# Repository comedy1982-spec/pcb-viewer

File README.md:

# AllinOneDesign

**요구사항 한 줄에서 시스템 다이어그램 → 회로 → PCB → 기구(하우징)까지, 브라우저 하나에서 AI와 함께 설계하는 단일 HTML 도구**입니다. 파일은 브라우저 안에서만 처리되며 서버로 전송되지 않습니다.

- 실행: `dist/index.html`을 브라우저로 엽니다 (3D·zip·엑셀 라이브러리만 CDN에서 불러오므로 인터넷 연결 필요).
- 사용 설명서: [docs/manual.html](docs/manual.html) · 기능 상세 노트(버전별): [docs/DETAILS.md](docs/DETAILS.md)
- 예제: SENSE-32, MCU DC 모터(MOTION-32 DEV), MCU BLDC 3상(MOTION-32 BLDC), AURIX TC364 인버터 — 첫 화면의 예제 칩으로 엽니다.

## 주요 기능

### 1. 단계별 설계 (신규 설계)
| 단계 | 하는 일 | 결과물 |
|---|---|---|
| **1 시스템 다이어그램** | 프로젝트 이름·요구사항을 적으면 AI가 분석하고, 빠진 필수 정보(전원·MCU·통신·기능·환경)는 **응답형 질문 카드**로 물어본 뒤 HW 블록 다이어그램을 그립니다. 블록·기능·인터페이스를 명령 또는 패널에서 편집합니다. | HW 블록 다이어그램 (SVG) |
| **2 회로** | 다이어그램을 **저가형 · 표준 · 확장형** 세 회로 안으로 풀어 BOM 참고가·부품 수·여유 MCU 핀·레귤레이터 손실·점수를 비교하고 하나를 고릅니다. 실제 부품 선정 · 넷리스트 · MCU 핀 배정 · 회로도가 만들어지며, **데이터시트 탭**에서 부품별 정리 페이지(HTML DB)를 봅니다. | 회로도(여러 시트) · 넷리스트 · BOM |
| **3 PCB** | 층 수(2–10) · 보드 크기(최소화/자동/직접) · 배치 전략을 고르면 자동 배치·배선합니다. 부품 끌어 옮기기·배선·비아·DRC·래츠네스트 편집, 내층을 포함한 **층별 보기**, 핀 스왑으로 회로와 함께 수정. | 배치·배선된 보드 (KiCad 저장) |
| **모터 파워 스테이지** | DC 모터 H-브리지(게이트 드라이버 ×2 + 외부 N-MOSFET ×4)·3상 인버터(×3 + ×6)를 전류 등급에 맞춰 FET 병렬·션트·전류 앰프·벌크·역전압 P-FET까지 회로로 생성, 트레이스 폭에 모터 전류 반영. | 회로도 · BOM |
| **부품 핀** | 라이브러리에 핀이 없으면 데이터시트 PDF를 올려 핀 표를 읽어 저장(pdf.js, 패키지별 표 선택, AI 모드 Claude 판독) — `datasheet <MPN>`, add part / replace, 라이브러리 버튼. | 핀 배열 → 회로 |
| **1 안전 목표** | ASIL ≠ QM이면 안전 목표(SG)를 고르고 위반 경로 블록에 태그, 구조 변형 3안(단일 MCU+외부 감시 · 메인+세이프티 MCU · ASIL 분해 2채널)을 DC·FTTI·원가로 비교해 적용, 규칙으로 검증(감지·독립 차단·FTTI·독립성·공통 원인). | SG 태그 · 검증 ✓/✗ |
| **4 기구 CAD** | 보드를 감싸는 보호 하우징을 Text-to-CAD로 설계합니다(시안 A 다이캐스팅·B 사출 스냅핏·C 압출 프로파일·D 하이브리드, 재질 6종·IP·진동·발열 조건, 구멍·글랜드·벤트·탭·리브·핀·각인, 둥근모따기/각모따기). 3D에서 요소를 **선택해 AI에게 지시**하고, 조립도·부품도(베이스/커버)·기구 BOM·SCAD/STL을 냅니다. | 하우징 3D · 도면 · BOM · SCAD |

기존 프로젝트(KiCad `.kicad_pcb`·회로도, PADS Logic 회로도, Gerber, 뷰어 JSON)도 같은 단계 표시줄로 오갑니다. 1단계는 보드에서 추출한 HW 블록 다이어그램입니다.

### 2. AI 설계 도우미
- 오른쪽 도킹 패널의 **설계 도우미**가 네 단계의 콘솔(시스템·회로도·배치/배선·Text-to-CAD)을 하나의 대화로 합칩니다. 결정론 모드는 문장을 규칙으로 명령으로 바꾸고, AI 모드는 Claude가 같은 명령을 골라 실행합니다.
- 설계를 바꾼 실행마다 **변경 요청 카드**가 붙습니다: 시스템·회로·PCB·HSIS·기구·BOM 영향, 변경 요약, 실행한 명령. **승인**하면 `CR-n` 리비전으로 기록되고, **되돌리기**는 그 실행만 정확히 되돌립니다.
- 기구 CAD에서는 3D나 형상 트리에서 요소를 고른 뒤(Shift/Ctrl 다중) "이거 M20으로 키우고 윗면은 R2"처럼 지시합니다.
- **등급 부품 자동 적용**: ASIL 프로젝트는 회로 생성 때 상용 부품을 핀 호환 차량용(AEC-Q100/Q101/Q200) 부품으로 바꾸고, `safety parts [--apply]`가 등급 미달·미상 부품과 대체품을 점검·일괄 교체합니다. 부품 레코드에 등급·온도·ASIL·FIT 필드(CSV·Claude 추정·API).
- **기능 안전(ASIL)**: 요구사항의 ASIL A~D를 읽어 시스템·블록 등급(배지·세이프 스테이트 경로·FFI 경계)을 다이어그램에 얹고, 등급별 권장 안전 메커니즘(전원 감시·외부 워치독·fault 리드백·SBC·이중 차단·리던던트 센서·2채널)을 블록으로 추가해 회로 부품(TPS3823 감시/워치독, 하이사이드 차단 스위치)까지 생성합니다. 회로·PCB 콘솔 `safety check`/`safety fmeda`가 등급별 회로 점검과 FIT·DC·SPFM·PMHF 추정을 내고 보고서·Excel·HSIS에 실립니다.
- **회로 해석(analyze)**: 전원 트리 · 디커플링 감사 · RC/LC·분압·LED 패턴 · 수동 소자 AC 주파수 응답 · DC 동작점(MNA) · IR drop · 신호 무결성 · 열 · EMC를 조회 명령으로 열어, 질문 모드의 Claude가 "필터 컷오프 얼마야?", "레일 전압 강하는?"에 계산값으로 답합니다.
- **아무 부품이나 추가**: "CC2420 추가해줘" → 라이브러리/Claude 추정의 핀 배열로 심볼을 만들고 전원·접지 자동 연결, 나머지 핀은 `connect`로, `apply`로 보드에(패키지 이름으로 풋프린트 생성).
- **보드 모양**: 사각형 외에 라운드·원형·타원·L자·T자·육각·팔각·다각형과 컷아웃(구멍) — 시작 카드에서 고르거나 `board shape …`/"원형 60mm로".
- **제품 프로필**: "EPS ECU 설계"처럼 제품만 적어도 표준 블록 구성(전원·SBC·락스텝 MCU·CAN-FD·인버터·페이즈 컷·센서 IF…)을 먼저 깔고, 블록별로 갈리는 것(타입·센서 IF·리던던시…)만 묻습니다. AI 모드는 어떤 제품이든, 규칙 모드는 EPS·BMS·BCM·인버터 템플릿.
- **로컬 AI**: claude.ai 밖(내려받은 파일·`npm run serve`)에서는 [Claude 허용] → 로컬 AI 설정에 API 키(또는 프록시)를 넣으면 같은 AI 모드가 Messages API로 동작합니다. `npm run serve:copilot`이면 API 키 없이 **GitHub Copilot** 구독(Copilot CLI 로그인)으로 동작합니다.
- **회로 보강 명령**: "HSIS 기준으로 테스트 포인트 전부 달아줘"(`tp`), "안 쓰는 핀 10k로 GND에"(`tie`), "전원 입력에 페라이트 비드"(`insert`), `add C --pins U1.12,GND`처럼 핀을 직접 지정 — AI 모드가 이 명령들로 풀어 실행하고 보드에 반영(`apply`)까지 합니다. TP는 HSIS 표의 TP 열·검사에 연결됩니다.
- **부품 교체(대화형)**: "U2를 AP2112K-3.3으로 바꿔줘"라고 하면 승인 부품 목록 → 내장 DB → Claude 추정 → 부품 API(Mouser·Nexar·사내 서버) 순으로 부품을 찾고, 핀 대응(이름·역할·번호)을 표로 확인받은 뒤 회로도·보드(풋프린트 자동 생성)·BOM·데이터시트·HSIS를 한 번에 바꿉니다. 머리글 **부품** 창에서 회사 승인 부품 목록(CSV/Excel)을 가져오고 추정 결과를 승인·내보냅니다.

### 3. 보기 · 분석
- **3D / TOP / BOTTOM / 층별(내층 포함) / 회로도**, 나란히 보기, 여러 보기를 격자로 띄우는 **새 창**(시스템 다이어그램·기구 3D·기구 도면·HSIS·시뮬레이션 포함, 메인 창과 연동).
- **지표 띠**: BOM 참고가, 가이드라인 점수, DRC·미배선, HSIS 정상/전체, 최고 Tj, 하우징 무게·IP — 누르면 해당 화면으로.
- **전체 보기**: 네 단계의 그림과 수치가 화살표로 이어진 한 화면, AI 바 포함.
- **시뮬레이션**: 전압 강하(IR drop), 신호 무결성, 열 분포, EMC/EMI, 회로 동작(MNA + 펌웨어 코시뮬레이션: LED·모터가 3D에서 움직임).
- **설계 가이드라인** 점검(회로·PCB 프리셋), DRC.

### 4. HSIS (HW/SW 인터페이스 사양)
- 엑셀 HSIS와 AUTOSAR ARXML을 읽어 **신호 표 · MCU 핀 맵 · 추적성(요구사항↔테스트) · 검사 결과 · 핀 추천(헝가리안 매칭) · MCAL 설정 · 테스트 케이스(SWE.6/SYS.4)**를 만들고 회로도·보드·펌웨어와 대조합니다.
- 보드에 HSIS가 없으면 MCU 핀과 넷으로 초안을 만듭니다.

### 5. 멀티보드 시스템
- 메인 + 센서 보드처럼 **보드 둘 이상을 커넥터로 잇는 제품**을 한 시스템으로 묶습니다. 머리글의 보드 선택 상자로 보드를 추가(파일·신규 설계·예제)하고 오갑니다.
- **시스템 연결** 탭: 보드·커넥터 짝으로 연결(케이블/B2B)을 만들고 핀을 번호·넷 이름·직접으로 매핑, 핀 수·짝 없는 핀·접지/전원/신호 충돌·레일 전압·차동 쌍 점검, 보드 연결도(SVG/PNG), 시스템 넷, 시스템 BOM(보드별 수량) → Excel·보고서.

### 6. 리비전 기록 · 비교
- 설계가 바뀌면 자동으로 리비전이 쌓이고(원인·단계·변경 요약 포함), 이름·단계(Proto~MP)·메모를 붙여 저장할 수 있습니다.
- **비교**: 요약 · 부품 · 배치 · 넷/핀 · **PCB 겹쳐 보기**(같음/A에만/B에만) · 다이어그램·계획 · HSIS · 기구. **원장** 보기는 리비전×영역 표.
- **복원**, 이력 JSON 내보내기/불러오기(Git에 함께 커밋).

### 7. 내보내기
- **프로젝트 저장 · 열기 · 이어서 하기**: 설계 중 어느 단계에서든 [저장](Ctrl+S)으로 전체 설계(모든 보드 · 요구사항 · 다이어그램 · 회로 안 · PCB · 기구 · HSIS, 열려 있던 단계)를 `.aod.json` 한 파일로 받고, [열기](Ctrl+O) · 첫 화면 · 파일 불러오기로 다시 엽니다. 작업은 브라우저에도 자동 저장돼, 새로 고침 뒤 첫 화면의 [이어서 하기]로 돌아옵니다.
- 회로도 교환: **PADS Logic ASCII**(.txt) 내보내기·가져오기, PADS Layout용 **PADS 넷리스트**(.asc), KiCad `.kicad_sch`. 회로도 파일만 넣으면 그 부품·넷으로 보드를 만들어 PCB 단계로 이어 갑니다.
- 그림: 2D 보드(층별)·회로도는 화면과 동일한 **SVG**, PNG, 시스템 다이어그램, 3D·기구 3D PNG, 기구 조립도·부품도, 모든 층 zip.
- 표: HSIS(시트별), BOM, 부품 배치, 넷리스트, 층 구성, 기구 BOM, 리비전 기록, 비교 결과 → **Excel**.
- **설계 보고서**: 항목을 골라 그림·표를 모두 담은 HTML 한 파일(브라우저 인쇄로 PDF). KiCad PCB/회로도 저장, OpenSCAD·STEP(AP214 솔리드 — SolidCraft·Fusion·SolidWorks·FreeCAD)·STL·HSIS CSV·MCAL 파일.

### 8. 실제 부품 데이터
- 부품 DB(제조사·사양·데이터시트 링크·참고 단가)와 MCU 핀 기능 DB(TC364DP, STM32F042), 부품당 한 레코드인 **데이터시트 DB**(원본 `datasheets/records/*.json` → 페이지 `datasheets/db/`, `npm run dsdb`; 회로 생성기의 후보 사양도 여기서 읽음).
- **부품 라이브러리**: 승인 부품 목록(CSV/Excel) · Claude 추정 · 부품 API 결과를 브라우저에 쌓아 두고 교체·데이터시트 탭에서 씁니다. 패키지 이름만으로 풋프린트(SOT-23-5, SOIC-14, QFN-24 4x4, DIP-8 …)를 만들어 보드에 올립니다.

## 화면 구성

```
┌ 머리: 프로젝트 · [전체] [1 시스템 · 2 회로 · 3 PCB · 4 기구] [HSIS] [시스템 연결] · 불러오기 · 내보내기 · 리비전 · 보기 전환 · 도우미 ┐
├ 지표 띠: BOM · 가이드라인 · DRC · HSIS · 최고 Tj · 시스템 연결 · 하우징                                                       ┤
├ 작업 공간 (단계마다 바뀜)                                            │ 도킹 패널: 설계 도우미 · 정보 · 시뮬레이션 · 데이터시트 ┤
│   레이어/보드 요약 · 3D/TOP/BOTTOM/층별/회로도 · 시스템 다이어그램 · 기구 CAD · HSIS │   (탭마다 새 창으로 뗄 수 있음)              │
└──────────────────────────────────────────────────────────────────┴──────────────────────────────────────────────┘
```

## 개발

```sh
npm run build     # src/ → dist/index.html (datasheets/db → dsdb.js 포함, Node 18+)
npm test          # 파서·회로도·시뮬레이션·HSIS·배치·배선·하우징·리비전·내보내기 테스트
npm run dsdb      # 데이터시트 HTML DB 번들 · npm run dsdb:init 초안 생성
npm run examples  # examples/ 다시 만들기 (python3 + openpyxl)
```

| 경로 | 내용 |
|---|---|
| `src/core/` | 보드 모델·파서(`pcb-core`), 편집(`pcbedit`), 자동 배치(`autoplace`), HW 아키텍처(`hwarch`), 시스템 다이어그램(`sysdiag`), 새 회로 설계(`newproj`), 하우징(`housing`), Text-to-CAD(`text2cad`), 가이드라인(`guide`), 리비전 스냅샷·비교(`revlog`), 멀티보드 시스템(`multiboard`), 부품 라이브러리·핀 대응(`partlib`), 풋프린트 생성(`fpgen`) |
| `src/route/autoroute.js` | 다층 자동 배선 |
| `src/sch/` | 회로도 파서·생성·편집 (KiCad, PADS Logic `pads.js`) |
| `src/sim/` | 전기·열·EMC 해석, MNA 회로 해석 |
| `src/hsis/` | HSIS 파서·검사·추적성, 핀 추천, MCAL, 테스트 케이스 생성 |
| `src/parts/` | 부품 DB, MCU 핀 DB, 데이터시트 DB 번들 |
| `src/fw/fw.js` | MCU 펌웨어 런타임 (샌드박스, 회로와 1 ms 코시뮬레이션) |
| `src/app/` | 화면: `viewer`(2D/3D), `newui`(단계·회로 안), `copilot`(도우미), `pcbui`·`pcbcli`(PCB 편집·CLI), `schui`·`schcli`, `mechui`(기구), `hsisui`, `simui`, `popui`(새 창), `exportui`, `revui`, `nextui`(지표·전체 보기·변경 요청·원장·분해), `iconui`, `mbui`(멀티보드), `partui`(부품 교체·라이브러리), `modeui`, `dsui`, `aimode` |
| `datasheets/records/` | 부품별 데이터시트 레코드(JSON, 원본) |
| `datasheets/db/` | 레코드에서 생성한 HTML 페이지 |
| `docs/` | 사용 설명서(`manual.html`), 기능 상세 노트(`DETAILS.md`), 화면 캡처(`img/`) |
| `test/` | `node --test` 테스트 |

모든 수치(열·진동·EMC·단가·하우징)는 초기 설계용 추정입니다. 양산 전에는 전문 도구와 시험으로 확인하세요.

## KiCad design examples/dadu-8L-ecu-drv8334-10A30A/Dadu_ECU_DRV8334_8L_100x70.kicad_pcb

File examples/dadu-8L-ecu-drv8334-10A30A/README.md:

# Dadu: ECU 커넥터 하나 · DRV8334 · 상시 10 A / 피크 30 A · 8층 100 × 70 mm

Dadu 3상 BLDC 컨트롤러(AURIX TC364, CAN-FD, 홀 센서)입니다. 차량 쪽 연결을 **Molex MX150 방수 20핀 커넥터 하나**로 모았고, 게이트 드라이버는 TI **DRV8334-Q1**입니다.

## ECU 커넥터 핀 (MX150 2열 20핀, 3.50 mm)
| 핀 | 신호 | 핀 | 신호 |
|---|---|---|---|
| 1 | BAT (12 V) | 11 | BAT |
| 2 | GND | 12 | GND |
| 3 | 9V (홀 센서 공급) | 13 | HALL_U |
| 4 | HALL_V | 14 | HALL_W |
| 5 | HALL_GND (센서 리턴) | 15 | SPARE_AIN (예비 아날로그 입력) |
| 6 | SPARE_PWM (예비 PWM 출력) | 16 | NC |
| 7 | CAN_H | 17 | CAN_L |
| 8 | U | 18 | U |
| 9 | V | 19 | V |
| 10 | W | 20 | W |

전력 신호(BAT · GND · U · V · W)는 접점 2개씩 병렬입니다(접점당 15 A, 피크 30 A). 품번과 풋프린트 치수는 Molex 34830 도면으로 확인해야 합니다.

## 만든 방법 (v1.102.0)
```
node scripts/pcbrun.cjs --profile Dadu --cur "~10 A (소형 팬 · 펌프)" \
  --param pwr_in.conn=ecu,gdrv3.driver=DRV8334,gdrv3.i=10,gdrv3.ipk=30,gdrv3.tpk=2 --add spare --w 100 --h 70 \
  --cmds "board layers 8; board size 100 70 --anchor center; reset --strategy compact --both --top sense,power --drv-gap 12 --seed 6; route"
```
배치 37 s, 배선 69 s(헤드리스)입니다.

## 결과 (2 oz · 상시 ΔT 20 °C · 피크 한도 40 °C)
| 넷 | 유효 폭 (필요 3.51 mm) | 상시 상승 | 피크 30 A 2 s 끝 |
|---|---|---|---|
| U | 5.82 mm | +4.5 °C | +10.8 °C |
| V | 4.40 mm | +7.2 °C | +18.8 °C |
| W | 8.90 mm | +2.2 °C | +4.6 °C |
| BAT (VIN_RAW) | 16.55 mm | +0.8 °C | +1.3 °C |

- 미연결 0, DRC 0, 아래층 부품 18개
- 전력 비아 16곳 모두 통과, 내층 평면 GND +1.3 °C · +12V +4.3 °C
- 역접속 FET은 피크 30 A라 D2PAK-7(IPB180P04P4L-02)입니다.

## 참고
- 같은 설정의 다른 시드(1 · 2 · 3 · 9)는 미연결 2–12개가 남았습니다. 이 구조는 아직 시드에 따라 결과가 크게 갈립니다.
- V 상은 MX150 3.5 mm 접점 열 사이 가운데라, 커넥터 구간 폭이 층당 2.2 mm입니다.
- DRV8334 주문 품번(E/Q 온도 등급)과 HTQFP 노출 패드 치수는 TI 패키지 도면으로 확인해야 합니다.

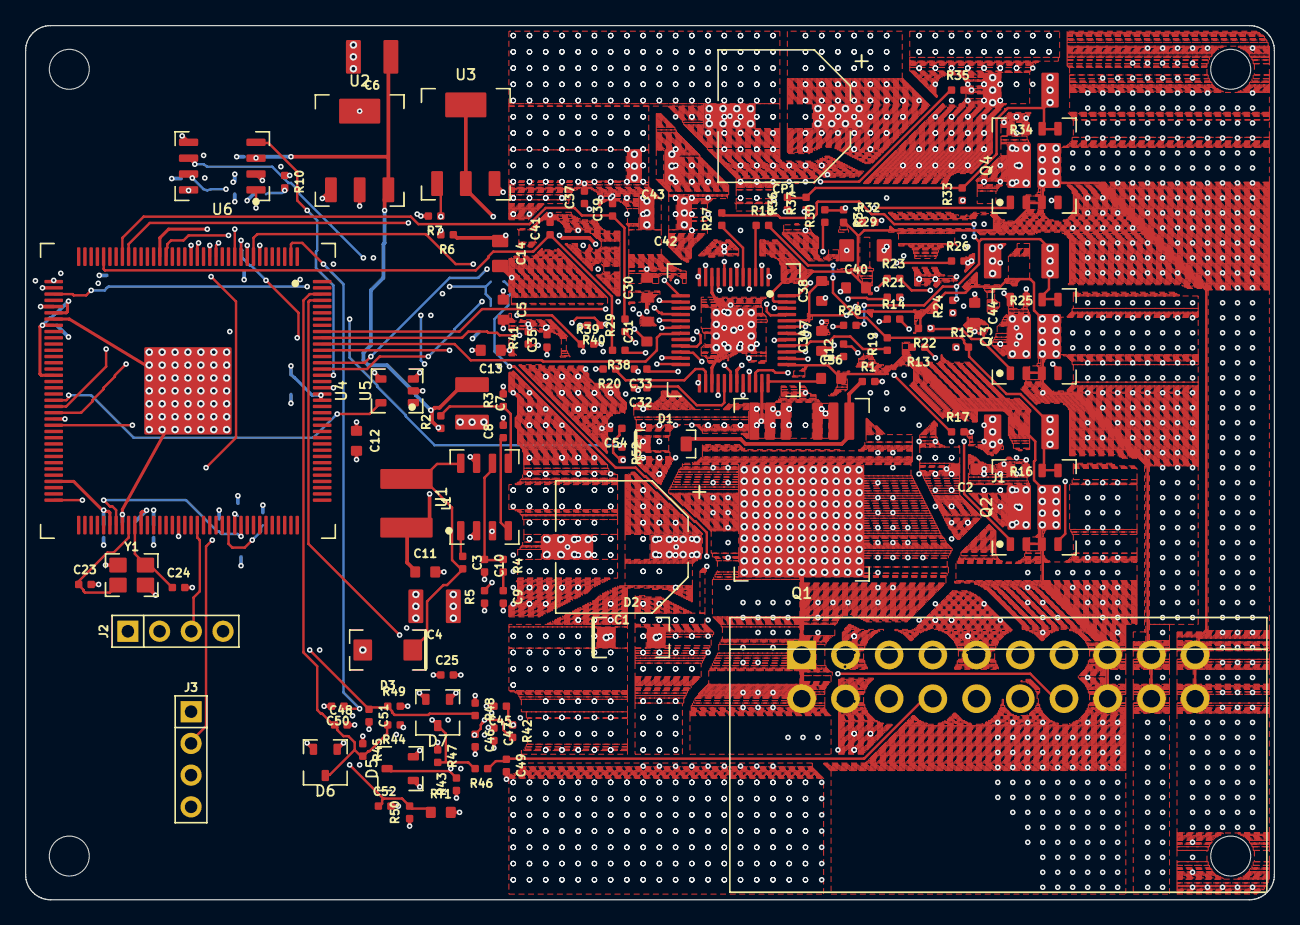
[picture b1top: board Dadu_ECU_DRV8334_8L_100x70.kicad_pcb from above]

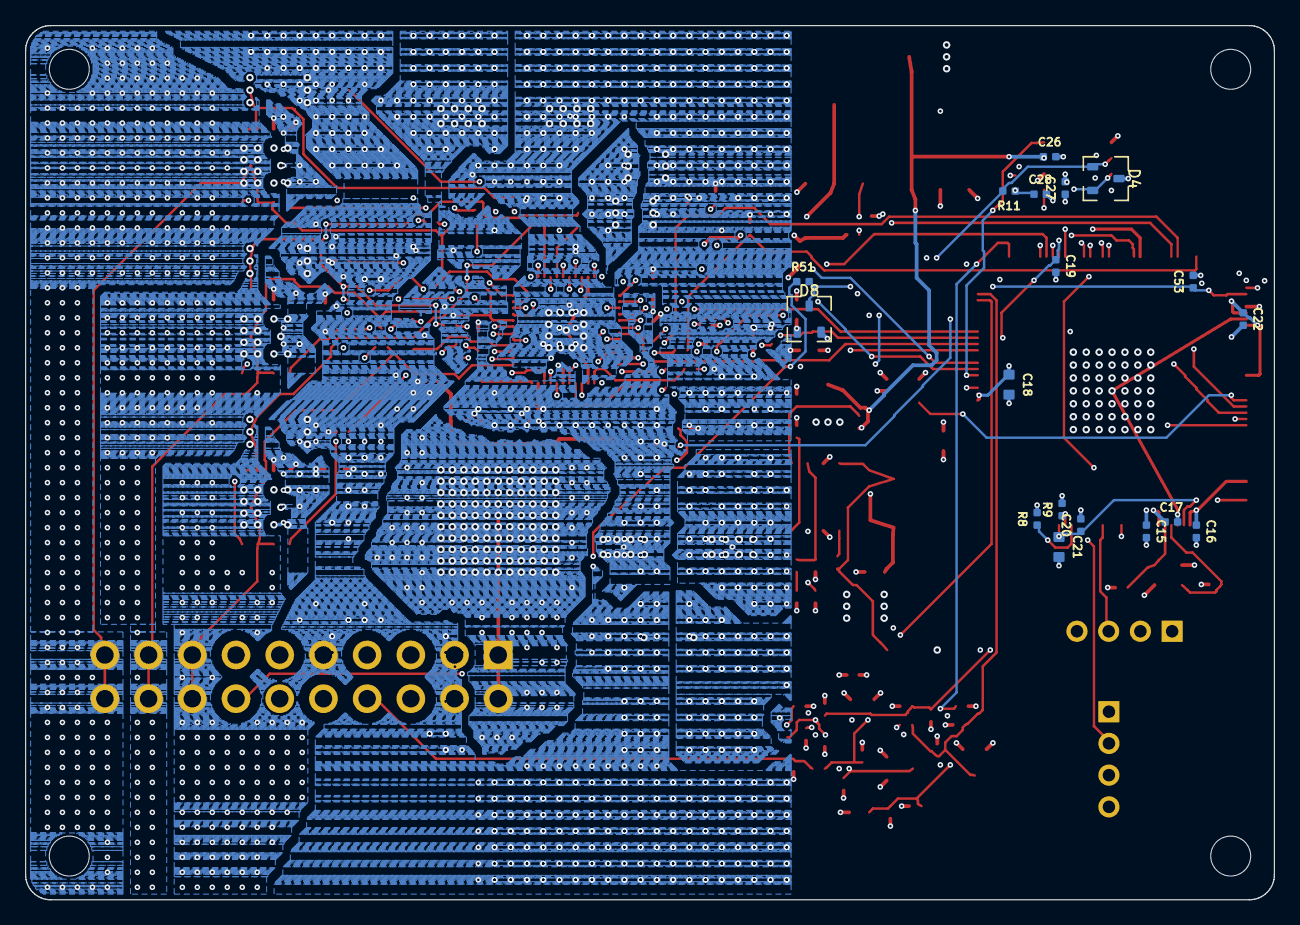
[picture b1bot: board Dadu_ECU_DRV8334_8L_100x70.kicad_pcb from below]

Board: 8 copper layers, 100.0 x 70.0 mm, 136 parts (18 on the bottom side), 98 nets.

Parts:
C1: 470µF; CP-SMD-10x10
C2, C5, C44: 100nF; 0603
C3, C15, C16, C17, C19, C20, C22, C25, C26, C27, C35, C51, C52: 100nF; 0402
C4, C6, C7: 22µF; 1210
C8, C53: 10nF; 0402
C9: 3.3nF; 0402
C10: 47pF; 0402
C11, C12, C18, C31: 10µF; 0603
C13, C30, C34, C36, C38, C40: 1µF; 0603
C14: 10µF; 0805
C21: 470nF; 0603
C23, C24: 12pF; 0402
C28: 4.7nF; 0402
C29: 10µF; 1206
C32, C33: 1µF; 0402
C37, C39, C41: 470pF; 0402
C42, C43: 2.2µF; 1210
C45, C46, C47, C48, C49, C50, C54: 1nF; 0402
CP1: 470µF; CP-SMD-10x10
D1: BZT52C12; SOD-123
D2: SMAJ15A; SMA
D3: MBRA340T3G; SMA
D4: PESD1CAN; SOT-23
D5, D6, D7, D8: BAT54S; SOT-23
H1, H2, H3, H4: MountingHole
J1: ECU; MX150-2x10-RA
J2: DAP; HDR-1x4
J3: UART; HDR-1x4
L1: 10µH; IND-5x5
Q1: IPB180P04P4L-02; TO-263-7
Q2, Q3, Q4: IAUC60N04S6N050H; TDSON-8-2FET
R1, R3, R8, R9, R13, R15, R22, R24, R31, R33, R39, R40, R41, R50: 10kΩ; 0402
R2: 52.3kΩ; 0402
R4: 76.8kΩ; 0402
R5, R48: 100kΩ; 0402
R6: 240Ω; 0402
R7: 1.5kΩ; 0402
R10, R11: 60.4Ω; 0402
R12, R14, R21, R23, R30, R32: 10Ω; 0402
R16, R25, R34: 2mΩ; 2010
R17, R18, R19, R26, R27, R28, R35, R36, R37: 0Ω; 0402
R20, R29, R38: 160Ω; 0402
R42, R44, R46, R51: 1kΩ; 0402
R43, R45, R47: 4.7kΩ; 0402
R49: 22kΩ; 0402
R52: 100Ω; 0402
RT1: NTC 10k; 0603
U1: TPS54331; SOIC-8
U2: AMS1117-3.3; SOT-223
U3: LM317; SOT-223
U4: TC364DP; TQFP-144
U5: TPS3823-33; SOT-23-5
U6: TLE9251V; SOIC-8
U7: DRV8334-Q1; QFP-48-EP-7x7-P0.5
Y1: 20MHz; XTAL-3225

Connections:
+3V3: C12.1, C15.1, C16.1, C17.1, C18.1, C22.1, C25.1, C27.1, C35.1, D5.2 (K2), D6.2 (K2), D7.2 (K2), D8.2 (K2), J2.1 (3V3), J3.4 (3V3), R8.2, R9.2, R39.2, R40.2, R43.1, R45.1, R47.1, R50.1, U2.2 (VOUT), U2.4 (VOUT), U4.23 (VEXT), U4.42 (VAREF1), U4.44 (VDDM), U4.52 (VEVRSB), U4.69 (VEXT), U4.78 (VEXT), U4.83 (VEXT), U4.125 (VEXT), U4.126 (VDDP3), U5.2 (VDD), U5.4 (MR), U6.5 (VIO), U7.23
+5V: C6.1, C7.1, C11.1, C26.1, L1.2, R2.1, U2.3 (VIN), U6.3 (VCC)
+9V: C14.1, J1.3 (9V), R6.1, U3.2 (VOUT), U3.4 (VOUT)
+12V: C1.1, C2.1, C4.1, C5.1, C13.1, C29.1, C30.1, C34.2, C42.1, C43.1, C44.1, CP1.1, D1.1 (K), D2.1 (K), Q1.2 (S), Q1.3 (S), Q1.5 (S), Q1.6 (S), Q1.7 (S), Q2.7 (BAT), Q2.8 (BAT), Q2.9 (BAT), Q3.7 (BAT), Q3.8 (BAT), Q3.9 (BAT), Q4.7 (BAT), Q4.8 (BAT), Q4.9 (BAT), R5.1, R48.1, U1.2 (VIN), U3.3 (VIN), U7.31, U7.35
BUCK_BOOT: C3.1, U1.1 (BOOT)
BUCK_COMP: C10.1, R4.1, U1.6 (COMP)
BUCK_EN: R5.2, U1.3 (EN)
BUCK_FB: R2.2, R3.1, U1.5 (VSENSE)
BUCK_RC: C9.1, R4.2
BUCK_SS: C8.1, U1.4 (SS)
BUCK_SW: C3.2, D3.1 (K), L1.1, U1.8 (PH)
CANH: D4.2 (CANH), J1.7 (CAN_H), R10.1, U6.7 (CANH)
CANL: D4.1 (CANL), J1.17 (CAN_L), R11.2, U6.6 (CANL)
CAN_RX: U4.129 (P13.1), U6.4 (RxD)
CAN_SPLIT: C28.1, R10.2, R11.1
CAN_STB: U4.57 (P33.1), U6.8 (STB)
CAN_TX: U4.11 (P00.0), U6.1 (TxD)
DBG_RX: J3.2 (RX), U4.17 (P00.6)
DBG_TX: J3.1 (TX), U4.18 (P00.7)
ESR0: R9.1, U4.98 (ESR0)
GND: C1.2, C2.2, C4.2, C5.2, C6.2, C7.2, C8.2, C9.2, C10.2, C11.2, C12.2, C13.2, C14.2, C15.2, C16.2, C17.2, C18.2, C19.2, C20.2, C21.2, C22.2, C23.2, C24.2, C25.2, C26.2, C27.2, C28.2, C29.2, C30.2, C31.2, C35.2, C37.2, C39.2, C41.2, C42.2, C43.2, C44.2, C45.2, C46.2, C47.2, C48.2, C49.2, C50.2, C51.2, C52.2, C53.2, C54.2, CP1.2, D2.2 (A), D3.2 (A), D4.3 (GND), D5.1 (A1), D6.1 (A1), D7.1 (A1), D8.1 (A1), J1.2 (GND), J1.5 (HALL_GND), J1.12 (GND), J2.4 (GND), J3.3 (GND), R1.2, R3.2, R7.2, R16.2, R17.2, R25.2, R26.2, R34.2, R35.2, R41.2, R49.2, RT1.2, U1.7 (GND), U2.1 (GND), U4.41 (VAGND1), U4.43 (VSSM), U4.80 (VSS), U4.145 (VSS (노출 패드)), U5.3 (GND), U6.2 (GND)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
LDO_ADJ: R6.2, R7.1, U3.1 (ADJ)
PH_CPH: C32.1, U7.29
PH_CPL: C32.2, U7.28
PH_CPTH: C33.1, U7.33
PH_CPTL: C33.2, U7.32
PH_DRVOFF: R40.1, U4.58 (P33.2), U7.9
PH_GVDD: C31.1, U7.30
PH_HALL_A: C46.1, D5.3 (K1/A2), R42.2, R43.2, U4.141 (P10.2)
PH_HALL_A_IN: C45.1, J1.13 (HALL_U), R42.1
PH_HALL_B: C48.1, D6.3 (K1/A2), R44.2, R45.2, U4.142 (P10.3)
PH_HALL_B_IN: C47.1, J1.4 (HALL_V), R44.1
PH_HALL_C: C50.1, D7.3 (K1/A2), R46.2, R47.2, U4.2 (P02.1)
PH_HALL_C_IN: C49.1, J1.14 (HALL_W), R46.1
PH_INH_U: U4.131 (P13.3), U7.11
PH_INH_V: U4.130 (P13.2), U7.13
PH_INH_W: U4.7 (P02.6), U7.15
PH_INL_U: U4.9 (P02.8), U7.12
PH_INL_V: U4.136 (P11.8), U7.14
PH_INL_W: U4.8 (P02.7), U7.16
PH_ISNS_U: C37.1, R20.2, U4.28 (AN35)
PH_ISNS_U_AMP: R20.1, U7.26
PH_ISNS_V: C39.1, R29.2, U4.29 (AN34)
PH_ISNS_V_AMP: R29.1, U7.25
PH_ISNS_W: C41.1, R38.2, U4.32 (AN28)
PH_ISNS_W_AMP: R38.1, U7.24
PH_NFAULT: R39.1, U4.15 (P00.4), U7.22
PH_NSCS: U4.60 (P33.4), U7.20
PH_NSLEEP: R41.1, U4.59 (P33.3), U7.21
PH_SCK: U4.134 (P11.6), U7.19
PH_SDI: U4.135 (P11.9), U7.18
PH_SDO: U4.133 (P11.3), U7.17
PH_U: C36.2, J1.8 (U), J1.18 (U), Q2.2 (PH), Q2.3 (PH), Q2.10 (PH), R13.2, U7.37
PH_U_HG: Q2.1 (G_HS), R12.2, R13.1
PH_U_HO: R12.1, U7.38
PH_U_LG: Q2.4 (G_LS), R14.2, R15.1
PH_U_LO: R14.1, U7.39
PH_U_LSS: R19.1, U7.40
PH_U_SNS: Q2.5 (GND), Q2.6 (GND), R15.2, R16.1, R18.2, R19.2
PH_U_SNSM: R17.1, U7.4
PH_U_SNSP: R18.1, U7.3
PH_U_VB: C36.1, U7.36
PH_V: C38.2, J1.9 (V), J1.19 (V), Q3.2 (PH), Q3.3 (PH), Q3.10 (PH), R22.2, U7.44
PH_VCP: C34.1, U7.34
PH_V_HG: Q3.1 (G_HS), R21.2, R22.1
PH_V_HO: R21.1, U7.43
PH_V_LG: Q3.4 (G_LS), R23.2, R24.1
PH_V_LO: R23.1, U7.42
PH_V_LSS: R28.1, U7.41
PH_V_SNS: Q3.5 (GND), Q3.6 (GND), R24.2, R25.1, R27.2, R28.2
PH_V_SNSM: R26.1, U7.6
PH_V_SNSP: R27.1, U7.5
PH_V_VB: C38.1, U7.45
PH_W: C40.2, J1.10 (W), J1.20 (W), Q4.2 (PH), Q4.3 (PH), Q4.10 (PH), R31.2, U7.47
PH_W_HG: Q4.1 (G_HS), R30.2, R31.1
PH_W_HO: R30.1, U7.48
PH_W_LG: Q4.4 (G_LS), R32.2, R33.1
PH_W_LO: R32.1, U7.1
PH_W_LSS: R37.1, U7.2
PH_W_SNS: Q4.5 (GND), Q4.6 (GND), R33.2, R34.1, R36.2, R37.2
PH_W_SNSM: R35.1, U7.8
PH_W_SNSP: R36.1, U7.7
PH_W_VB: C40.1, U7.46
PORST: R8.1, U4.97 (PORST)
SPARE_AIN: C53.1, D8.3 (K1/A2), R51.2, U4.39 (AN17)
SPARE_AIN_IN: J1.15 (SPARE_AIN), R51.1
SPARE_PWM: R52.1, U4.14 (P00.3)
SPARE_PWM_OUT: C54.1, J1.6 (SPARE_PWM), R52.2
TCK: J2.3 (TCK), U4.92 (TCK)
TEMP: C52.1, R50.2, RT1.1, U4.38 (AN20)
TMS: J2.2 (TMS), U4.89 (TMS)
VDD: C19.1, C20.1, C21.1, U4.10 (VDD), U4.22 (VDD), U4.72 (VDD), U4.79 (VDD), U4.99 (VDD), U4.127 (VDD)
VIN_PG: D1.2 (A), Q1.1 (G), R1.1
VIN_RAW: J1.1 (BAT), J1.11 (BAT), Q1.4 (D)
VMON: C51.1, R48.2, R49.1, U4.37 (AN21)
WDI: U4.56 (P33.0), U5.5 (WDI)
XTAL1: C23.1, U4.81 (XTAL1), Y1.1
XTAL2: C24.1, U4.82 (XTAL2), Y1.3

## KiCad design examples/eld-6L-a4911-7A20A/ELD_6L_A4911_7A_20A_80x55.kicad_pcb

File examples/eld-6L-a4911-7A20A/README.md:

# ELD only — A4911 H-브리지 · 상시 7 A / 피크 20 A (2 s) · ECU 커넥터 하나 · 6층 양면 80 × 55 mm (자동 배선 완료)

Dadu 기반 ELD 솔레노이드 ECU. 12 V 입력, TC364 · CAN-FD · PMIC, PCB 위 센서는 NTC 하나.
A4911(3상 드라이버)의 A·B 레그로 H-브리지(하프브리지 IAUC60N04S6N050H ×2, 레그 션트 2 mΩ ×2), C 레그는 비워 두고 SPI로 그 고장(VC · CHO · CLO · OC3)을 마스크.

## ECU 커넥터 — Molex MX150 방수 직각 PCB 헤더 2×6 (34830 계열)
맞물림 피치 3.50 mm · 1.5 mm 단자 · 접점당 최대 정상 전류 15 A · IP67/IP69K · −40…125 °C. 피크 20 A가 15 A를 넘어 전력 신호는 2접점(같은 열의 안·바깥 핀)씩.

| 열 (보드 안쪽 → 끝) | 1 | 2 | 3 | 4 | 5 | 6 |
|---|---|---|---|---|---|---|
| 안쪽 줄 (핀 1–6) | BAT | GND | IGN | CAN_H | ELD+ | ELD− |
| 바깥 줄 (핀 7–12) | BAT | GND | NC | CAN_L | ELD+ | ELD− |

품번 `0348301201`은 계열 규칙(0348300801 = 8핀)으로 추정, 풋프린트는 가정 치수(3.50 mm 격자, 구멍 1.4 mm) — 출도 전 Molex 도면으로 확인. 상대 커넥터는 MX150 2열 12핀 리셉터클(33472 계열). J2 · J3은 보드 안 디버그 헤더(DAP · UART).

| 파일 | 내용 |
|---|---|
| `ELD_6L_A4911_7A_20A_80x55.kicad_pcb` | KiCad 보드 파일 |
| `top.jpg` / `bottom.jpg` | 위층 / 아래층 화면 |

## 만든 방법 (v1.98.0)
```
node scripts/pcbrun.cjs --profile "ELD only" --cur "~7 A (ELD 솔레노이드)" --w 80 --h 55 \
  --cmds "board layers 6; board size 80 55 --anchor center; reset --strategy compact --both --seed 5; route"
```
기능 구획은 기본(권장)입니다. 배치 47 s · 배선 24 s (헤드리스).

## 결과 (2 oz · 상시 ΔT 20 °C · 피크 한도 40 °C)
| 넷 | 유효 폭 (필요 2.3 mm) | 피크 20 A 2 s 끝 상승 |
|---|---|---|
| HB_A (ELD+) | 6.1 mm | +4.4 °C |
| HB_B (ELD−) | 9.96 mm | +1.6 °C |
| VIN_RAW (BAT) | 14.8 mm | +0.7 °C |

- 내층 평면 GND · +12V +2.9 °C, 전력 비아 12곳 모두 통과(션트 R16 · R25 GND 비아 5 · 6개). 미연결 0 · DRC 0 · 아래층 부품 36개.
- 같은 조건 시드 4도 통과, 시드 1 · 2 · 6은 신호 미배선 3–4개.
- v1.98.0 전에는 ELD−(HB_B)가 ELD+ FET 옆을 지나며 0.2 mm로 막혀(먼저 자란 ELD+ 동박이 통로를 다 차지) 모든 시드가 실패했습니다. 출력마다 통로(lane)를 먼저 확보하도록 고쳤습니다.

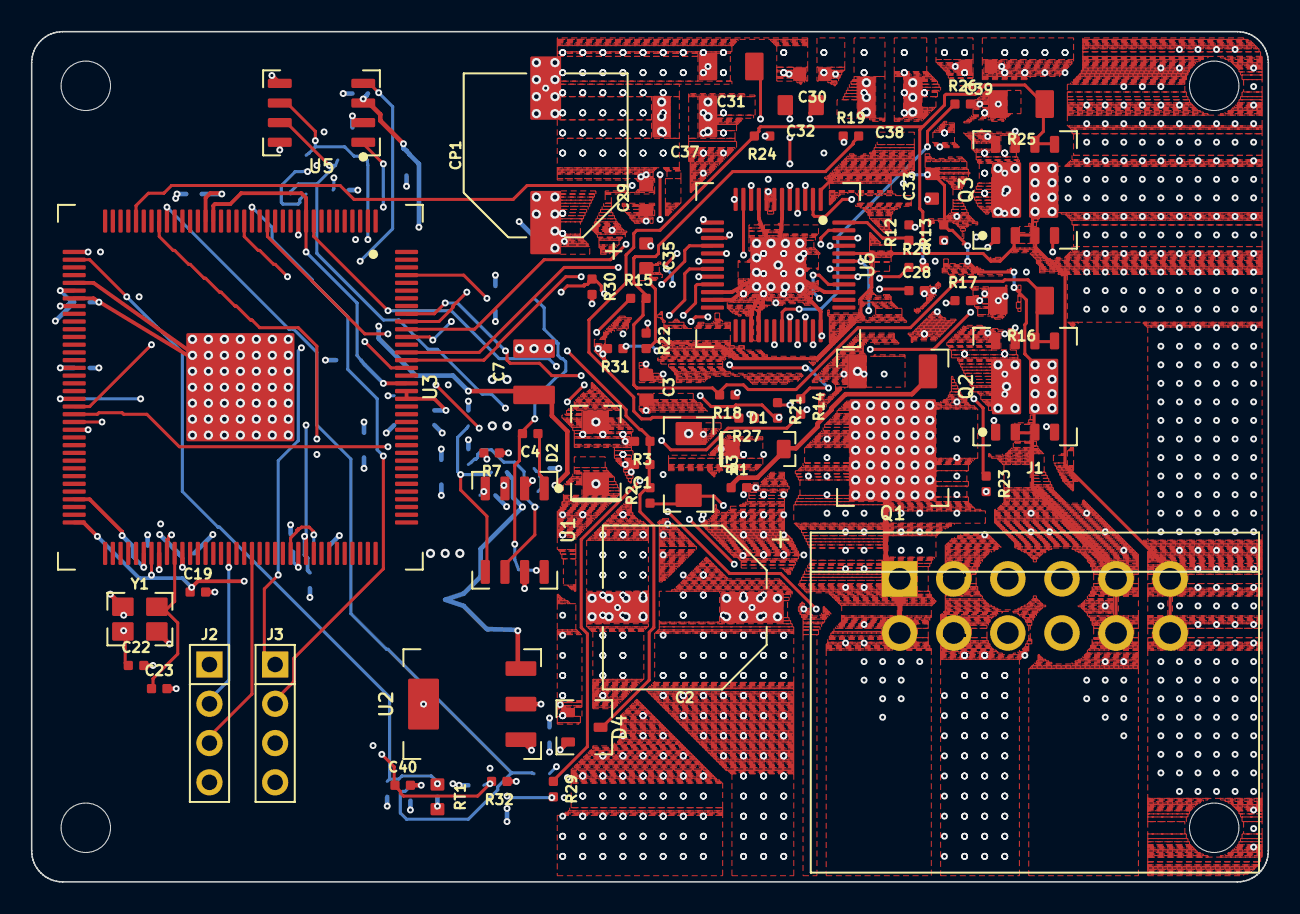
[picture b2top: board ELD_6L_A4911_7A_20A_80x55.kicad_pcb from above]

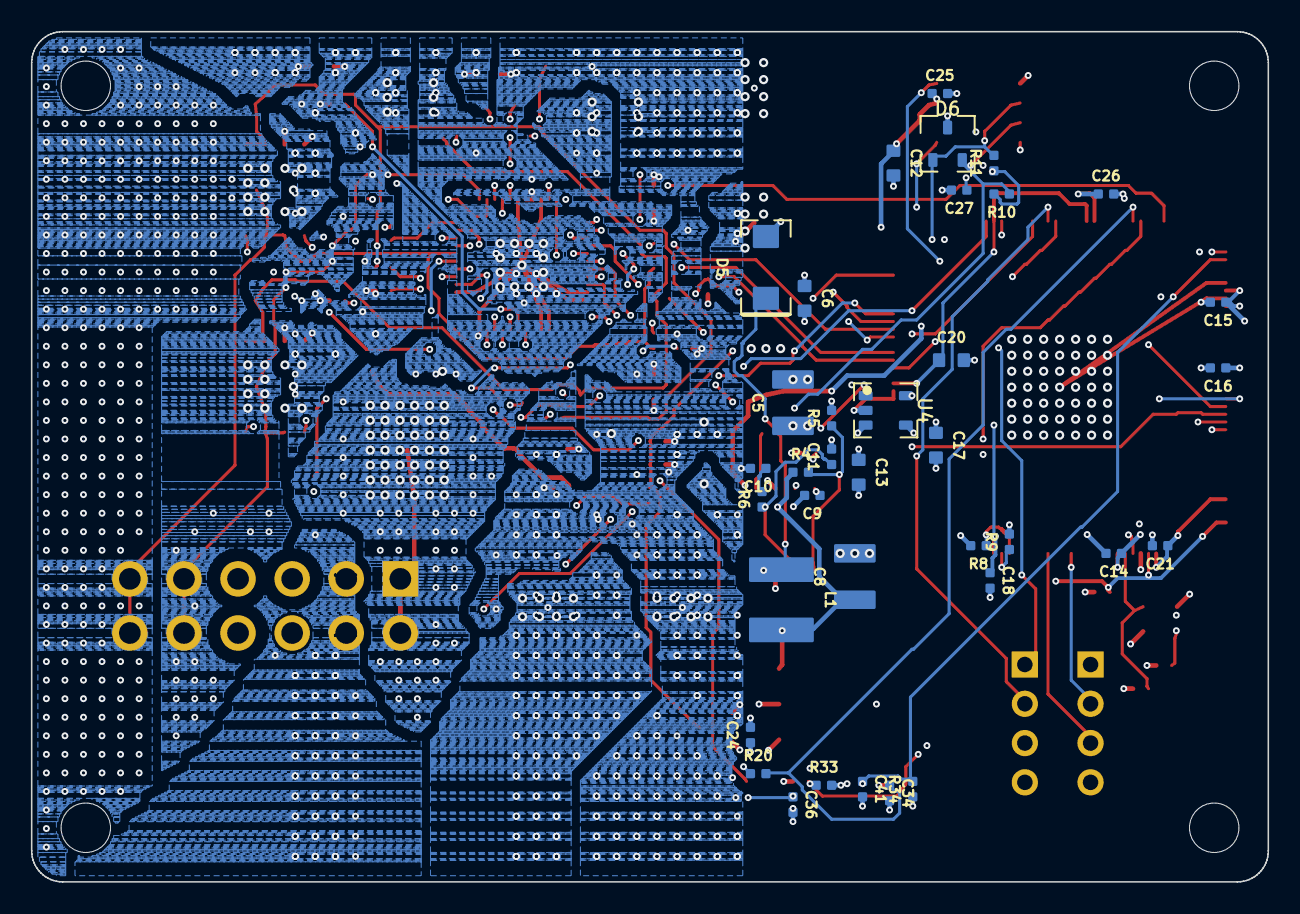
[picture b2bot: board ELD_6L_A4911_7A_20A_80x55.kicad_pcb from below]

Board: 6 copper layers, 80.0 x 55.0 mm, 101 parts (36 on the bottom side), 73 nets.

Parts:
C1, C9: 10nF; 0402
C2: 470µF; CP-SMD-10x10
C3, C6, C29, C30, C39: 100nF; 0603
C4, C14, C15, C16, C18, C19, C21, C24, C25, C26, C28, C40, C41: 100nF; 0402
C5, C7, C8: 22µF; 1210
C10: 3.3nF; 0402
C11: 47pF; 0402
C12, C13, C17: 10µF; 0603
C20: 470nF; 0603
C22, C23: 12pF; 0402
C27: 4.7nF; 0402
C31: 22µF; 1206
C32: 470nF; 0805
C33, C35: 68nF; 0603
C34, C36: 1nF; 0402
C37, C38: 2.2µF; 1210
CP1: 470µF; CP-SMD-10x10
D1: BZT52C12; SOD-123
D2: SMAJ15A; SMA
D3: SMAJ15CA; SMA
D4: BAT54S; SOT-23
D5: MBRA340T3G; SMA
D6: PESD1CAN; SOT-23
H1, H2, H3, H4: MountingHole
J1: ECU; MX150-2x6-RA
J2: DAP; HDR-1x4
J3: UART; HDR-1x4
L1: 10µH; IND-5x5
Q1: SQD50P04-09L; TO-252
Q2, Q3: IAUC60N04S6N050H; TDSON-8-2FET
R1, R3, R5, R8, R9, R13, R15, R22, R24, R30, R31, R34: 10kΩ; 0402
R2: 33kΩ; 0402
R4: 52.3kΩ; 0402
R6: 76.8kΩ; 0402
R7, R32: 100kΩ; 0402
R10, R11: 60.4Ω; 0402
R12, R14, R21, R23: 10Ω; 0402
R16, R25: 2mΩ; 1206
R17, R18, R19, R26, R27, R28: 0Ω; 0402
R20, R29: 1kΩ; 0402
R33: 22kΩ; 0402
RT1: NTC 10k; 0603
U1: TPS54331; SOIC-8
U2: AMS1117-3.3; SOT-223
U3: TC364DP; TQFP-144
U4: TPS3823-33; SOT-23-5
U5: TLE9251V; SOIC-8
U6: A4911; QFP-48-EP-7x7-P0.5
Y1: 20MHz; XTAL-3225

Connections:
+3V3: C13.1, C14.1, C15.1, C16.1, C17.1, C21.1, C24.1, C26.1, D4.2 (K2), J2.1 (3V3), J3.4 (3V3), R8.2, R9.2, R30.2, R34.1, U2.2 (VOUT), U2.4 (VOUT), U3.23 (VEXT), U3.42 (VAREF1), U3.44 (VDDM), U3.52 (VEVRSB), U3.69 (VEXT), U3.78 (VEXT), U3.83 (VEXT), U3.125 (VEXT), U3.126 (VDDP3), U4.2 (VDD), U4.4 (MR), U5.5 (VIO)
+5V: C7.1, C8.1, C12.1, C25.1, L1.2, R4.1, U2.3 (VIN), U5.3 (VCC)
+12V: C2.1, C3.1, C5.1, C6.1, C29.1, C30.1, C37.1, C38.1, C39.1, CP1.1, D1.1 (K), D2.1 (K), Q1.3 (S), Q2.7 (BAT), Q2.8 (BAT), Q2.9 (BAT), Q3.7 (BAT), Q3.8 (BAT), Q3.9 (BAT), R7.1, R32.1, U1.2 (VIN), U6.7 (VBB), U6.8 (VBRG)
BUCK_BOOT: C4.1, U1.1 (BOOT)
BUCK_COMP: C11.1, R6.1, U1.6 (COMP)
BUCK_EN: R7.2, U1.3 (EN)
BUCK_FB: R4.2, R5.1, U1.5 (VSENSE)
BUCK_RC: C10.1, R6.2
BUCK_SS: C9.1, U1.4 (SS)
BUCK_SW: C4.2, D5.1 (K), L1.1, U1.8 (PH)
CANH: D6.2 (CANH), J1.4 (CAN_H), R10.1, U5.7 (CANH)
CANL: D6.1 (CANL), J1.10 (CAN_L), R11.2, U5.6 (CANL)
CAN_RX: U3.129 (P13.1), U5.4 (RxD)
CAN_SPLIT: C27.1, R10.2, R11.1
CAN_STB: U3.57 (P33.1), U5.8 (STB)
CAN_TX: U3.11 (P00.0), U5.1 (TxD)
DBG_RX: J3.2 (RX), U3.17 (P00.6)
DBG_TX: J3.1 (TX), U3.18 (P00.7)
ESR0: R9.1, U3.98 (ESR0)
GND: C1.2, C2.2, C3.2, C5.2, C6.2, C7.2, C8.2, C9.2, C10.2, C11.2, C12.2, C13.2, C14.2, C15.2, C16.2, C17.2, C18.2, C19.2, C20.2, C21.2, C22.2, C23.2, C24.2, C25.2, C26.2, C27.2, C28.2, C29.2, C30.2, C31.2, C34.2, C36.2, C37.2, C38.2, C39.2, C40.2, C41.2, CP1.2, D2.2 (A), D3.1 (A1), D4.1 (A1), D5.2 (A), D6.3 (GND), J1.2 (GND), J1.8 (GND), J2.4 (GND), J3.3 (GND), R1.2, R3.2, R5.2, R16.2, R17.2, R25.2, R26.2, R31.2, R33.2, RT1.2, U1.7 (GND), U2.1 (GND), U3.41 (VAGND1), U3.43 (VSSM), U3.80 (VSS), U3.145 (VSS (노출 패드)), U4.3 (GND), U5.2 (GND), U6.6 (GND), U6.9 (GND), U6.22 (HC), U6.23 (LC), U6.27 (CS3P), U6.28 (CS3M), U6.36 (LSSC), U6.39 (SC), U6.49 (PAD), Y1.2, Y1.4
HB_A: C33.2, J1.5 (ELD+), J1.11 (ELD+), Q2.2 (PH), Q2.3 (PH), Q2.10 (PH), R13.2, U6.1 (SA)
HB_A_HG: Q2.1 (G_HS), R12.2, R13.1
HB_A_HO: R12.1, U6.48 (GHA)
HB_A_LG: Q2.4 (G_LS), R14.2, R15.1
HB_A_LO: R14.1, U6.47 (GLA)
HB_A_LSS: R19.1, U6.46 (LSSA)
HB_A_SNS: Q2.5 (GND), Q2.6 (GND), R15.2, R16.1, R18.2, R19.2
HB_A_SNSM: R17.1, U6.34 (CS1M)
HB_A_SNSP: R18.1, U6.33 (CS1P)
HB_A_VB: C33.1, U6.2 (CA)
HB_B: C35.2, J1.6 (ELD−), J1.12 (ELD−), Q3.2 (PH), Q3.3 (PH), Q3.10 (PH), R22.2, U6.44 (SB)
HB_B_HG: Q3.1 (G_HS), R21.2, R22.1
HB_B_HO: R21.1, U6.43 (GHB)
HB_B_LG: Q3.4 (G_LS), R23.2, R24.1
HB_B_LO: R23.1, U6.42 (GLB)
HB_B_LSS: R28.1, U6.41 (LSSB)
HB_B_SNS: Q3.5 (GND), Q3.6 (GND), R24.2, R25.1, R27.2, R28.2
HB_B_SNSM: R26.1, U6.31 (CS2M)
HB_B_SNSP: R27.1, U6.30 (CS2P)
HB_B_VB: C35.1, U6.45 (CB)
HB_CC_UNUSED: C28.1, U6.40 (CC)
HB_CP1: C32.1, U6.4 (CP1)
HB_CP2: C32.2, U6.5 (CP2)
HB_DIAG: R30.1, U3.141 (P10.2), U6.17 (DIAG)
HB_EN: R31.1, U3.58 (P33.2), U6.11 (ENABLE)
HB_INH_A: U3.131 (P13.3), U6.18 (HA)
HB_INH_B: U3.130 (P13.2), U6.20 (HB)
HB_INL_A: U3.9 (P02.8), U6.19 (LA)
HB_INL_B: U3.136 (P11.8), U6.21 (LB)
HB_ISNS_A: C34.1, R20.2, U3.28 (AN35)
HB_ISNS_A_AMP: R20.1, U6.35 (CS1O)
HB_ISNS_B: C36.1, R29.2, U3.29 (AN34)
HB_ISNS_B_AMP: R29.1, U6.32 (CS2O)
HB_ISNS_OOS: U3.32 (AN28), U6.10 (OOS)
HB_RESETN: U3.59 (P33.3), U6.12 (RESETn)
HB_SCK: U3.134 (P11.6), U6.14 (SCK)
HB_SDI: U3.135 (P11.9), U6.15 (SDI)
HB_SDO: U3.133 (P11.3), U6.16 (SDO)
HB_STRN: U3.60 (P33.4), U6.13 (STRn)
HB_VREG: C31.1, U6.3 (VREG)
IGN_DET: C1.1, D4.3 (K1/A2), R2.2, R3.1, U3.15 (P00.4)
IGN_IN: D3.2 (A2), J1.3 (IGN), R2.1
PORST: R8.1, U3.97 (PORST)
TCK: J2.3 (TCK), U3.92 (TCK)
TEMP: C41.1, R34.2, RT1.1, U3.38 (AN20)
TMS: J2.2 (TMS), U3.89 (TMS)
VDD: C18.1, C19.1, C20.1, U3.10 (VDD), U3.22 (VDD), U3.72 (VDD), U3.79 (VDD), U3.99 (VDD), U3.127 (VDD)
VIN_PG: D1.2 (A), Q1.1 (G), R1.1
VIN_RAW: J1.1 (BAT), J1.7 (BAT), Q1.2 (D)
VMON: C40.1, R32.2, R33.1, U3.37 (AN21)
WDI: U3.56 (P33.0), U4.5 (WDI)
XTAL1: C22.1, U3.81 (XTAL1), Y1.1
XTAL2: C23.1, U3.82 (XTAL2), Y1.3

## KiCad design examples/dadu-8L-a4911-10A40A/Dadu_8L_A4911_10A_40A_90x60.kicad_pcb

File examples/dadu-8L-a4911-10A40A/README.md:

# Dadu — A4911 · 상시 10 A / 피크 40 A (2 s) · 8층 양면 90 × 60 mm (자동 배선 완료)

상시(연속) 상전류 10 A, 기동 · 구속 피크 40 A가 2초 이내인 조건. 손실 · 발열과 상시 패턴 폭은 10 A로, MOSFET · 션트 범위 · 단자 · 피크 패턴 폭 · 비아는 40 A · 2 s로 정했습니다.

| 파일 | 내용 |
|---|---|
| `Dadu_8L_A4911_10A_40A_90x60.kicad_pcb` | KiCad 보드 파일 |
| `top.jpg` / `bottom.jpg` | 위층 / 아래층(좌우 반전 보기) 화면 |

## 만든 방법 (v1.80.1)
```
node scripts/pcbrun.cjs --cur "~10 A (소형 팬 · 펌프)" --param "gdrv3.driver=A4911,gdrv3.ipk=40,gdrv3.tpk=2" \
  --cmds "board layers 8; board size 90 60 --anchor center; reset --strategy compact --both --seed 11; route"
```

## 결과 (2 oz · 상시 ΔT 20 °C · 피크 한도 40 °C)
필요 폭 4.44 mm = 상시 10 A IPC 폭(2.36 mm)보다 넓게 — 상시 +7.1 °C에 피크 40 A 2 s 동안 +32.9 °C를 더해 40 °C 이내.

| 넷 | 유효 폭 (위 + 아래) | 상시 상승 | 피크 끝 상승 |
|---|---|---|---|
| PH_U | 9.95 mm | +1.9 °C | +8.5 °C |
| PH_V | 9.90 mm | +1.9 °C | +8.5 °C |
| PH_W | 7.49 mm | +3.0 °C | +14.6 °C |
| VIN_RAW | 17.93 mm | +0.7 °C | +2.7 °C |
| 상 → 션트 | 패드 직결 | — | — |

- 내층 평면: GND 2층 · +12V 1층 — 상시 +1.5 / +4.6 °C, 피크 끝 +1.9 / +6.2 °C
- 단자 비아(층을 바꾸는 몫): 전부 통과. 전력 패드 안 비아 0.6/0.3 mm
- 미연결 0 · DRC 0 · 아래층 부품 44개 · 션트 1 mΩ 2010(피크 40 mV · 1.6 W 2 s ≤ 단시간 과부하 1.875 W)

## 미세 피치 핀 탈출 순서 (v1.80.1)
이전 시드 23 결과는 미연결 2곳(SPI SDO · V상 게이트)이 남았습니다. SDO는 0.5 mm 피치 QFP 두 개(TC364 · A4911)에서 SCK · SDI 사이에 낀 핀이라, 이웃이 먼저 배선되며 양쪽 핀 앞 자리를 다 차지해 한 가닥도 나가지 못했습니다. 배선 순서에 "연속된 신호 핀 구간의 가운데 핀부터" 규칙을 넣은 뒤 같은 시드 23은 미연결 1, 시드 11은 미연결 0이 되었습니다.

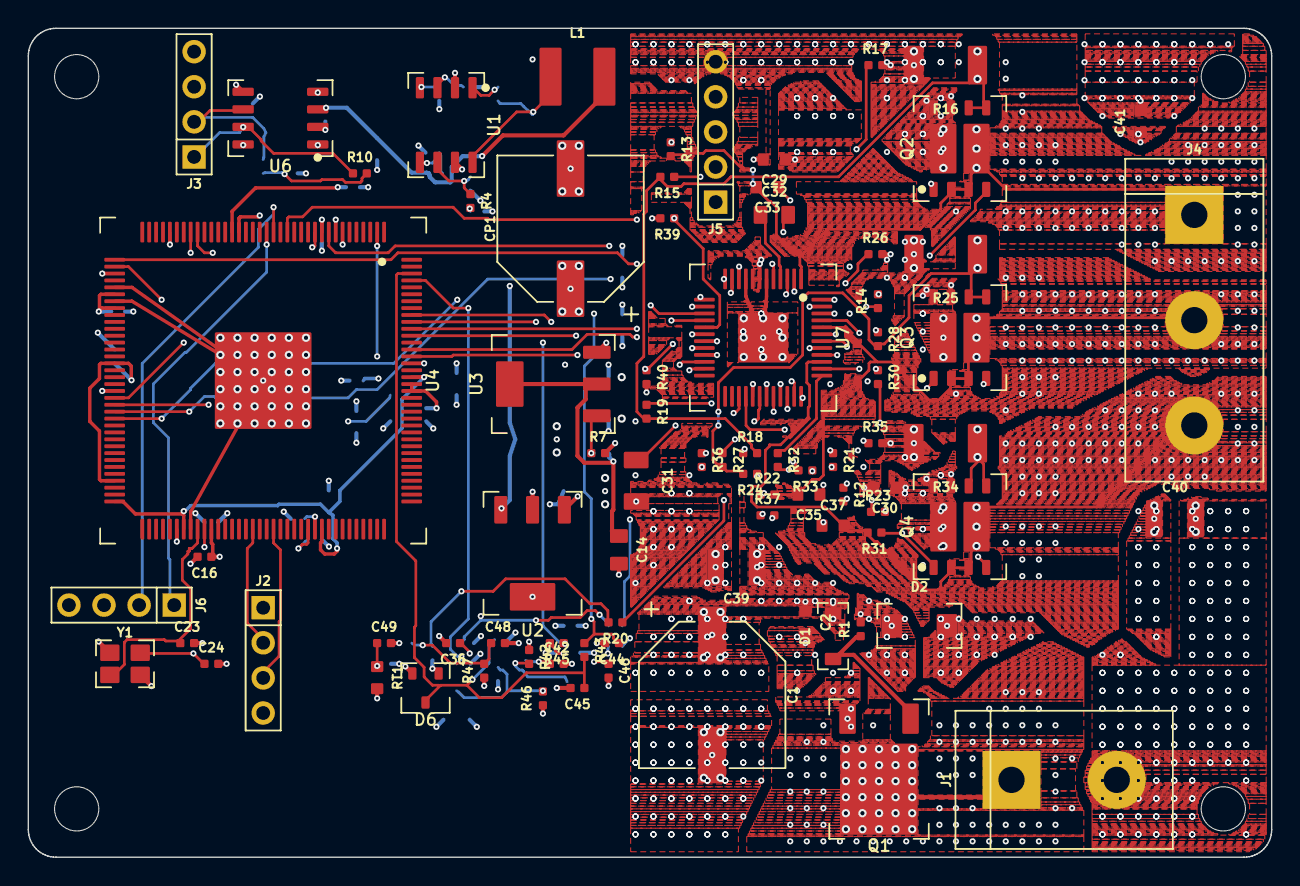
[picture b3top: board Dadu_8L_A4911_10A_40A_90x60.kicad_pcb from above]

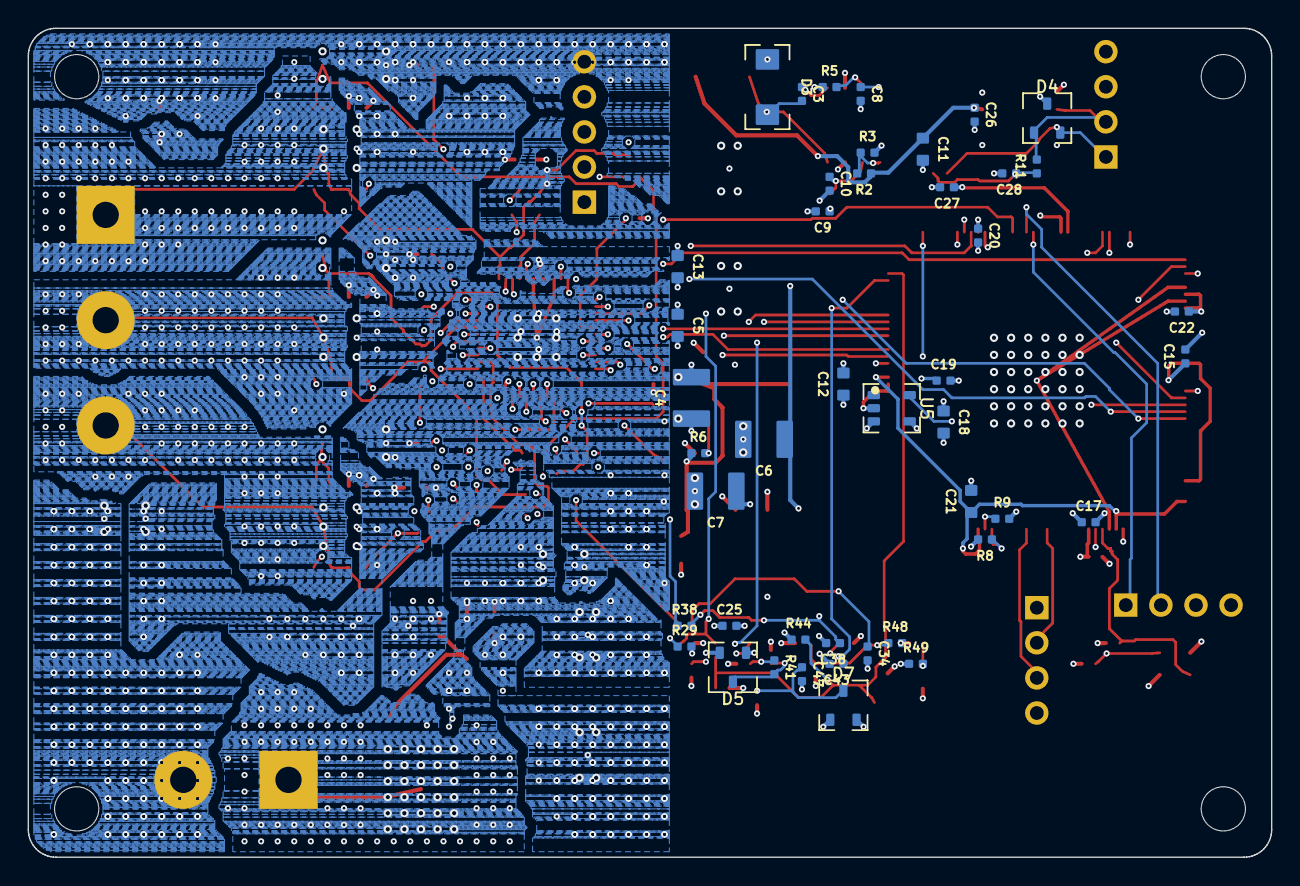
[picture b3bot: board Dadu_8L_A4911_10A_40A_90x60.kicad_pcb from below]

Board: 8 copper layers, 90.0 x 60.0 mm, 130 parts (44 on the bottom side), 92 nets.

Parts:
C1: 470µF; CP-SMD-10x10
C2, C5, C29, C30, C41: 100nF; 0603
C3, C15, C16, C17, C19, C20, C22, C25, C26, C27, C48, C49: 100nF; 0402
C4, C6, C7: 22µF; 1210
C8: 10nF; 0402
C9: 3.3nF; 0402
C10: 47pF; 0402
C11, C12, C18: 10µF; 0603
C13: 1µF; 0603
C14: 10µF; 0805
C21: 470nF; 0603
C23, C24: 12pF; 0402
C28: 4.7nF; 0402
C31: 22µF; 1206
C32: 470nF; 0805
C33, C35, C37: 68nF; 0603
C34, C36, C38, C42, C43, C44, C45, C46, C47: 1nF; 0402
C39, C40: 2.2µF; 1210
CP1: 470µF; CP-SMD-10x10
D1: BZT52C12; SOD-123
D2: SMAJ15A; SMA
D3: SS34; SMA
D4: PESD1CAN; SOT-23
D5, D6, D7: BAT54S; SOT-23
H1, H2, H3, H4: MountingHole
J1: 12V 입력; TERM-2-7.62
J2: DAP; HDR-1x4
J3: CAN; HDR-1x4
J4: 모터 상; TERM-3-7.62
J5: 홀; HDR-1x5
J6: UART; HDR-1x4
L1: 10µH; IND-5x5
Q1: SQD50P04-09L; TO-252
Q2, Q3, Q4: IAUC60N04S6N050H; TDSON-8-2FET
R1, R3, R8, R9, R13, R15, R22, R24, R31, R33, R39, R40, R49: 10kΩ; 0402
R2: 52.3kΩ; 0402
R4: 76.8kΩ; 0402
R5, R47: 100kΩ; 0402
R6: 240Ω; 0402
R7: 1.5kΩ; 0402
R10, R11: 60.4Ω; 0402
R12, R14, R21, R23, R30, R32: 10Ω; 0402
R16, R25, R34: 1mΩ; 2010
R17, R18, R19, R26, R27, R28, R35, R36, R37: 0Ω; 0402
R20, R29, R38, R41, R43, R45: 1kΩ; 0402
R42, R44, R46: 4.7kΩ; 0402
R48: 22kΩ; 0402
RT1: NTC 10k; 0603
U1: TPS54331; SOIC-8
U2: AMS1117-3.3; SOT-223
U3: LM317; SOT-223
U4: TC364DP; TQFP-144
U5: TPS3823-33; SOT-23-5
U6: TLE9251V; SOIC-8
U7: A4911; QFP-48-EP-7x7-P0.5
Y1: 20MHz; XTAL-3225

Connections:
+3V3: C12.1, C15.1, C16.1, C17.1, C18.1, C22.1, C25.1, C27.1, D5.2 (K2), D6.2 (K2), D7.2 (K2), J2.1 (3V3), J6.4 (3V3), R8.2, R9.2, R39.2, R42.1, R44.1, R46.1, R49.1, U2.2 (VOUT), U2.4 (VOUT), U4.23 (VEXT), U4.42 (VAREF1), U4.44 (VDDM), U4.52 (VEVRSB), U4.69 (VEXT), U4.78 (VEXT), U4.83 (VEXT), U4.125 (VEXT), U4.126 (VDDP3), U5.2 (VDD), U5.4 (MR), U6.5 (VIO)
+5V: C6.1, C7.1, C11.1, C26.1, L1.2, R2.1, U2.3 (VIN), U6.3 (VCC)
+9V: C14.1, J5.1 (9V), R6.1, U3.2 (VOUT), U3.4 (VOUT)
+12V: C1.1, C2.1, C4.1, C5.1, C13.1, C29.1, C30.1, C39.1, C40.1, C41.1, CP1.1, D1.2 (K), D2.2 (K), Q1.3 (S), Q2.7 (BAT), Q2.8 (BAT), Q2.9 (BAT), Q3.7 (BAT), Q3.8 (BAT), Q3.9 (BAT), Q4.7 (BAT), Q4.8 (BAT), Q4.9 (BAT), R5.1, R47.1, U1.2 (VIN), U3.3 (VIN), U7.7 (VBB), U7.8 (VBRG)
BUCK_BOOT: C3.1, U1.1 (BOOT)
BUCK_COMP: C10.1, R4.1, U1.6 (COMP)
BUCK_EN: R5.2, U1.3 (EN)
BUCK_FB: R2.2, R3.1, U1.5 (VSENSE)
BUCK_RC: C9.1, R4.2
BUCK_SS: C8.1, U1.4 (SS)
BUCK_SW: C3.2, D3.2 (K), L1.1, U1.8 (PH)
CANH: D4.2 (CANH), J3.1 (CANH), R10.1, U6.7 (CANH)
CANL: D4.1 (CANL), J3.2 (CANL), R11.2, U6.6 (CANL)
CAN_RX: U4.129 (P13.1), U6.4 (RxD)
CAN_SPLIT: C28.1, R10.2, R11.1
CAN_STB: U4.57 (P33.1), U6.8 (STB)
CAN_TX: U4.11 (P00.0), U6.1 (TxD)
DBG_RX: J6.2 (RX), U4.17 (P00.6)
DBG_TX: J6.1 (TX), U4.18 (P00.7)
ESR0: R9.1, U4.98 (ESR0)
GND: C1.2, C2.2, C4.2, C5.2, C6.2, C7.2, C8.2, C9.2, C10.2, C11.2, C12.2, C13.2, C14.2, C15.2, C16.2, C17.2, C18.2, C19.2, C20.2, C21.2, C22.2, C23.2, C24.2, C25.2, C26.2, C27.2, C28.2, C29.2, C30.2, C31.2, C34.2, C36.2, C38.2, C39.2, C40.2, C41.2, C42.2, C43.2, C44.2, C45.2, C46.2, C47.2, C48.2, C49.2, CP1.2, D2.1 (A), D3.1 (A), D4.3 (GND), D5.1 (A1), D6.1 (A1), D7.1 (A1), J1.2 (GND), J2.4 (GND), J3.3 (GND), J5.5 (GND), J6.3 (GND), R1.2, R3.2, R7.2, R16.2, R17.2, R25.2, R26.2, R34.2, R35.2, R40.2, R48.2, RT1.2, U1.7 (GND), U2.1 (GND), U4.41 (VAGND1), U4.43 (VSSM), U4.80 (VSS), U4.145 (VSS (노출 패드)), U5.3 (GND), U6.2 (GND), U7.6 (GND), U7.9 (GND), U7.49 (PAD), Y1.2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
LDO_ADJ: R6.2, R7.1, U3.1 (ADJ)
PH_CP1: C32.1, U7.4 (CP1)
PH_CP2: C32.2, U7.5 (CP2)
PH_DIAG: R39.1, U4.15 (P00.4), U7.17 (DIAG)
PH_EN: R40.1, U4.58 (P33.2), U7.11 (ENABLE)
PH_HALL_A: C43.1, D5.3 (K1/A2), R41.2, R42.2, U4.141 (P10.2)
PH_HALL_A_IN: C42.1, J5.2 (H1), R41.1
PH_HALL_B: C45.1, D6.3 (K1/A2), R43.2, R44.2, U4.142 (P10.3)
PH_HALL_B_IN: C44.1, J5.3 (H2), R43.1
PH_HALL_C: C47.1, D7.3 (K1/A2), R45.2, R46.2, U4.2 (P02.1)
PH_HALL_C_IN: C46.1, J5.4 (H3), R45.1
PH_INH_U: U4.131 (P13.3), U7.18 (HA)
PH_INH_V: U4.130 (P13.2), U7.20 (HB)
PH_INH_W: U4.7 (P02.6), U7.22 (HC)
PH_INL_U: U4.9 (P02.8), U7.19 (LA)
PH_INL_V: U4.136 (P11.8), U7.21 (LB)
PH_INL_W: U4.8 (P02.7), U7.23 (LC)
PH_ISNS_OOS: U4.37 (AN21), U7.10 (OOS)
PH_ISNS_U: C34.1, R20.2, U4.28 (AN35)
PH_ISNS_U_AMP: R20.1, U7.35 (CS1O)
PH_ISNS_V: C36.1, R29.2, U4.29 (AN34)
PH_ISNS_V_AMP: R29.1, U7.32 (CS2O)
PH_ISNS_W: C38.1, R38.2, U4.32 (AN28)
PH_ISNS_W_AMP: R38.1, U7.29 (CS3O)
PH_RESETN: U4.59 (P33.3), U7.12 (RESETn)
PH_SCK: U4.134 (P11.6), U7.14 (SCK)
PH_SDI: U4.135 (P11.9), U7.15 (SDI)
PH_SDO: U4.133 (P11.3), U7.16 (SDO)
PH_STRN: U4.60 (P33.4), U7.13 (STRn)
PH_U: C33.2, J4.1 (U), Q2.2 (PH), Q2.3 (PH), Q2.10 (PH), R13.2, U7.1 (SA)
PH_U_HG: Q2.1 (G_HS), R12.2, R13.1
PH_U_HO: R12.1, U7.48 (GHA)
PH_U_LG: Q2.4 (G_LS), R14.2, R15.1
PH_U_LO: R14.1, U7.47 (GLA)
PH_U_LSS: R19.1, U7.46 (LSSA)
PH_U_SNS: Q2.5 (GND), Q2.6 (GND), R15.2, R16.1, R18.2, R19.2
PH_U_SNSM: R17.1, U7.34 (CS1M)
PH_U_SNSP: R18.1, U7.33 (CS1P)
PH_U_VB: C33.1, U7.2 (CA)
PH_V: C35.2, J4.2 (V), Q3.2 (PH), Q3.3 (PH), Q3.10 (PH), R22.2, U7.44 (SB)
PH_VREG: C31.1, U7.3 (VREG)
PH_V_HG: Q3.1 (G_HS), R21.2, R22.1
PH_V_HO: R21.1, U7.43 (GHB)
PH_V_LG: Q3.4 (G_LS), R23.2, R24.1
PH_V_LO: R23.1, U7.42 (GLB)
PH_V_LSS: R28.1, U7.41 (LSSB)
PH_V_SNS: Q3.5 (GND), Q3.6 (GND), R24.2, R25.1, R27.2, R28.2
PH_V_SNSM: R26.1, U7.31 (CS2M)
PH_V_SNSP: R27.1, U7.30 (CS2P)
PH_V_VB: C35.1, U7.45 (CB)
PH_W: C37.2, J4.3 (W), Q4.2 (PH), Q4.3 (PH), Q4.10 (PH), R31.2, U7.39 (SC)
PH_W_HG: Q4.1 (G_HS), R30.2, R31.1
PH_W_HO: R30.1, U7.38 (GHC)
PH_W_LG: Q4.4 (G_LS), R32.2, R33.1
PH_W_LO: R32.1, U7.37 (GLC)
PH_W_LSS: R37.1, U7.36 (LSSC)
PH_W_SNS: Q4.5 (GND), Q4.6 (GND), R33.2, R34.1, R36.2, R37.2
PH_W_SNSM: R35.1, U7.28 (CS3M)
PH_W_SNSP: R36.1, U7.27 (CS3P)
PH_W_VB: C37.1, U7.40 (CC)
PORST: R8.1, U4.97 (PORST)
TCK: J2.3 (TCK), U4.92 (TCK)
TEMP: C49.1, R49.2, RT1.1, U4.39 (AN17)
TMS: J2.2 (TMS), U4.89 (TMS)
VDD: C19.1, C20.1, C21.1, U4.10 (VDD), U4.22 (VDD), U4.72 (VDD), U4.79 (VDD), U4.99 (VDD), U4.127 (VDD)
VIN_PG: D1.1 (A), Q1.1 (G), R1.1
VIN_RAW: J1.1 (+), Q1.2 (D)
VMON: C48.1, R47.2, R48.1, U4.38 (AN20)
WDI: U4.56 (P33.0), U5.5 (WDI)
XTAL1: C23.1, U4.81 (XTAL1), Y1.1
XTAL2: C24.1, U4.82 (XTAL2), Y1.3
